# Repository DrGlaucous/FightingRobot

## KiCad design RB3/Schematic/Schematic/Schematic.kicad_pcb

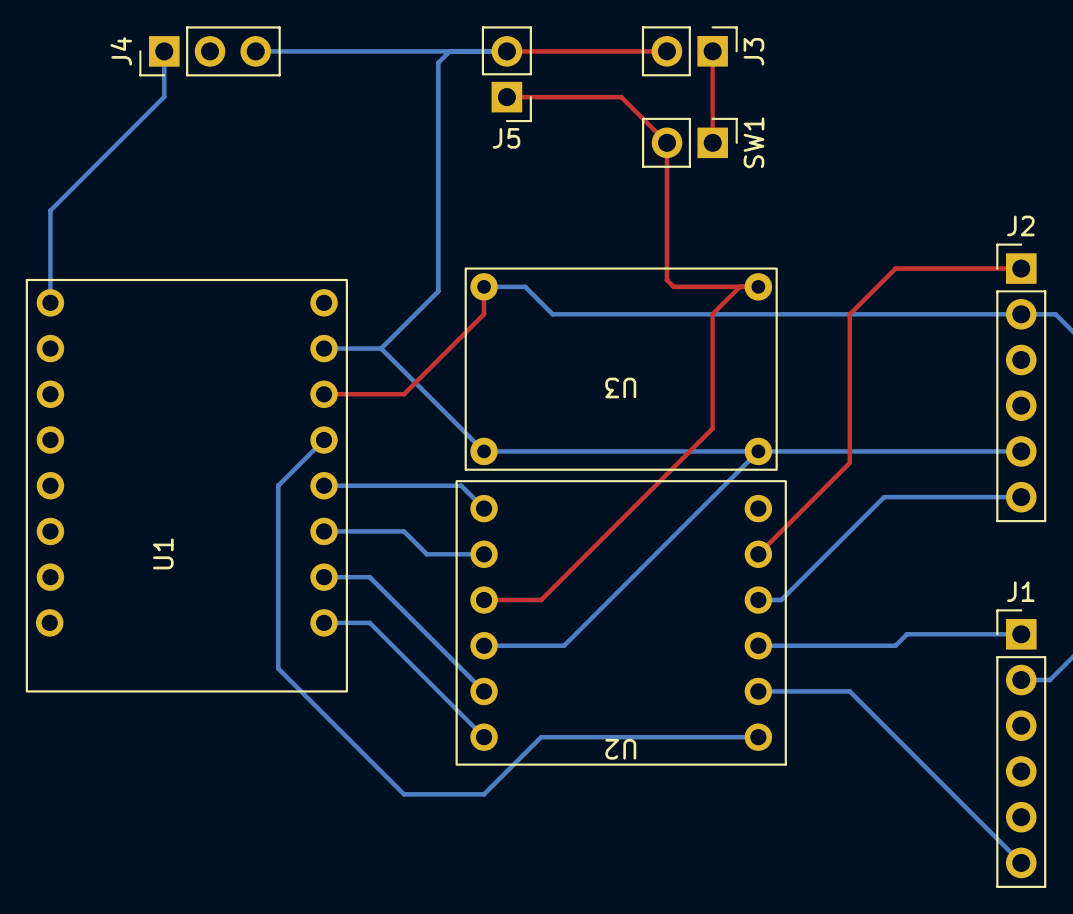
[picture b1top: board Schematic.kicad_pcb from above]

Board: 2 copper layers, 9 parts (0 on the bottom side), 18 nets.

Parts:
J1, J2: Motor 1; PinHeader_1x06_P2.54mm_Vertical
J3: Battery; PinHeader_1x02_P2.54mm_Vertical
J4: ESC; PinHeader_1x03_P2.54mm_Vertical
J5: ESC_PWR; PinHeader_1x02_P2.54mm_Vertical
SW1: MAIN_CUTOFF; PinHeader_1x02_P2.54mm_Vertical
U1: ESP32-C3-SuperMini_PLUS
U2: HW-627
U3: Mini360

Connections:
+3.3V: J1.2, J2.2, U1.14 (3v3), U3.4 (OUT)
+BATT: J3.1, SW1.1
/+BATT SW: J5.1, SW1.2, U2.9 (VMOT), U3.2 (IN)
/ESC: J4.1, U1.1 (D5)
/M1 A: J1.1 (Motor_2), U2.3 (OUT2)
/M1 B: J1.6 (M1), U2.2 (OUT1)
/M1 Control A: U1.9 (D0), U2.12 (IN4)
/M1 Control B: U1.10 (D1), U2.11 (IN3)
/M1 EA: J1.4, U1.5 (D9)
/M1 EB: J1.3, U1.4 (D8)
/M2 A: J2.1 (Motor_2), U2.5 (OUT4)
/M2 B: J2.6 (M1), U2.4 (OUT3)
/M2 Control A: U1.11 (D2), U2.8 (IN2)
/M2 Control B: U1.12 (D3), U2.7 (IN1)
/M2 EA: J2.4, U1.3 (D7)
/M2 EB: J2.3, U1.2 (D6)
/SLEEP: U1.13 (D4), U2.1 (SLEEP)
GND: J1.5, J2.5, J3.2, J4.3, J5.2, U1.15 (Gnd), U2.10 (GND), U3.1 (GND), U3.3 (GND)

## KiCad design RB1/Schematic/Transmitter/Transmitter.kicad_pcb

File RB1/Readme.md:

# Remote Vehicle repository

This is where I put everything relating to designing a small, "antweight" combat robot.

## Firmware
Currently, the firmware is programmed in platform.io around the STM32 architecture.
The vehicle communicates to the controller using the RFM69HW radio module, which is both inexpensive and has excellent transmission range.

The "Transmitter" module decodes [PPM signals](http://flyingeinstein.com/index.php/articles/58-ppm-explained) from the controller and sends their digital values over the radio to the vehicle. There *are* recievers that output PPM directly without the need for the RFM middleman, but those are expensive and radio-specific. The extra range those modules would provide would be moot in the context of miniature combat robots. The analog transmitters additionally do not provide the customization abillity the digital transmiter has.

The work with RFM69 radios builds upon my previous project where I made an [inexpensive iClicker alternative using just the radio and an STM32](https://github.com/DrGlaucous/LittleBuddy). That repository better outlines how the STM32 should be connected to the RFM69 module.

---

<details>
  <summary style="font-size:100%;"><i><b>Notes for me</b></i></summary>

### Future Goals
Either use an ESP32 on the vehicle-side, or add bidirectional DShot to the STM32, so the vehicle's motor will provide telemetry.

### Mobility
With the transmitter, more flexible motion can be implemented.

Current suggestion: 3 wheeled omniwheel wheelbase

### Weapons

Rotating offset platic blade on one side, must not be below or above the robot's dirve train so it can drive upside down or rightside up.

Or long, plastic wedge attached to a servo motor for flipping other robots.

</details>

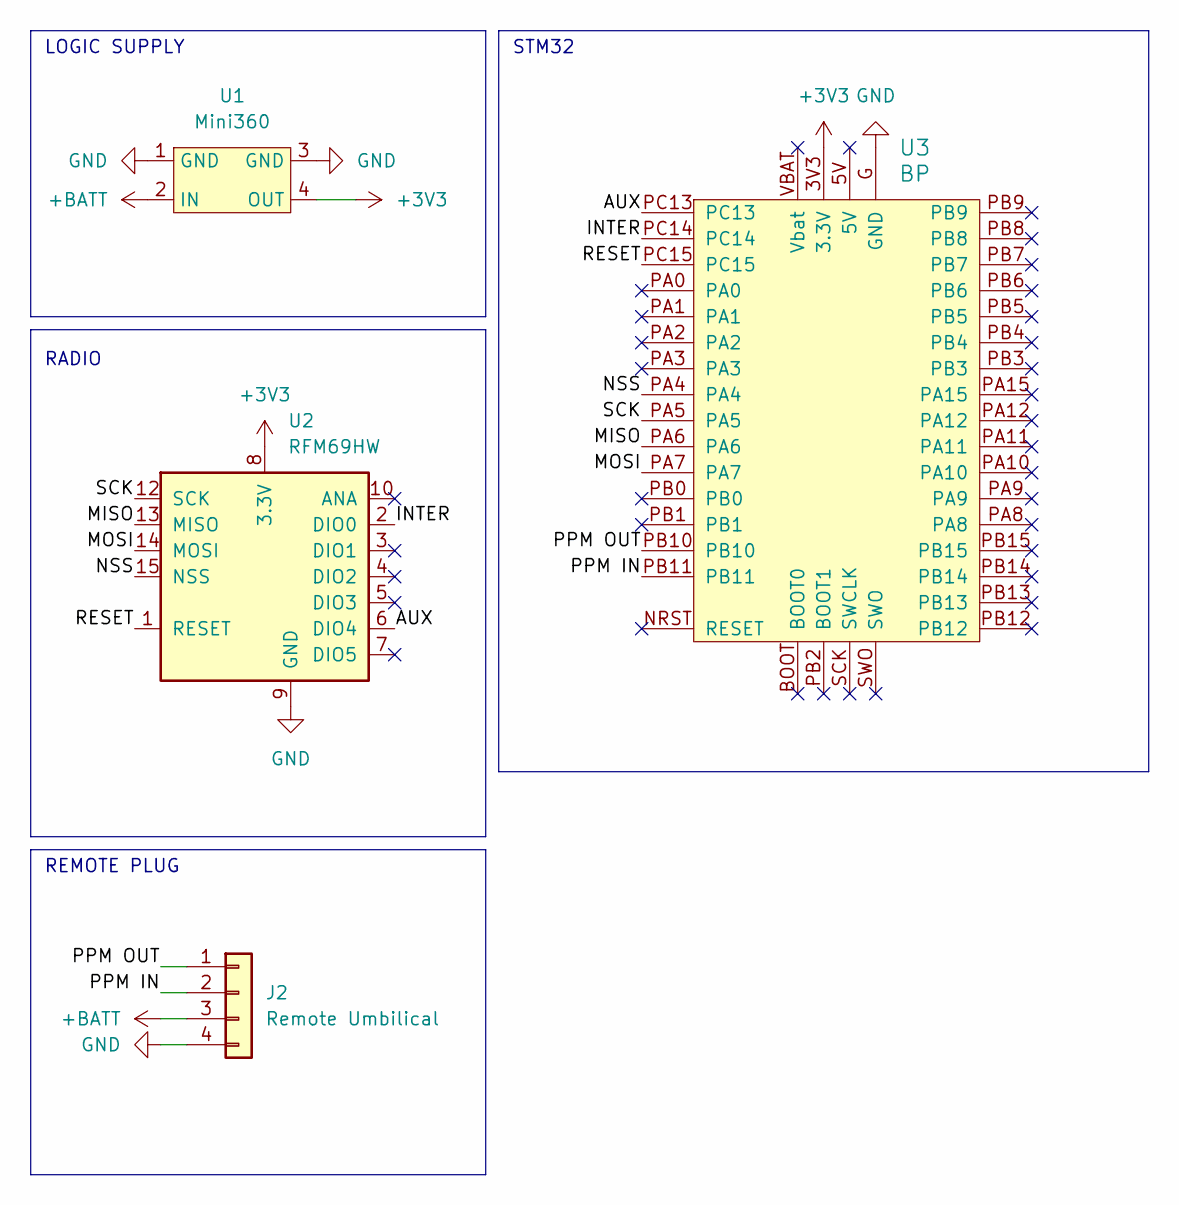
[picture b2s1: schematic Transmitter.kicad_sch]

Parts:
J2: Remote Umbilical; PinHeader_1x04_P2.54mm_Vertical
U1: Mini360
U2: RFM69HW; HOPERF_RFM69HW
U3: BP; blue_pill

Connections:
+3V3: U1.4 (OUT), U2.8 (3.3V), U3.3V3 (3.3V)
+BATT: J2.3, U1.2 (IN)
/AUX: U2.6 (DIO4), U3.PC13
/INTER: U2.2 (DIO0), U3.PC14
/MISO: U2.13 (MISO), U3.PA6
/MOSI: U2.14 (MOSI), U3.PA7
/NSS: U2.15 (NSS), U3.PA4
/PPM IN: J2.2, U3.PB11
/PPM OUT: J2.1, U3.PB10
/RESET: U2.1 (RESET), U3.PC15
/SCK: U2.12 (SCK), U3.PA5
GND: J2.4, U1.1 (GND), U1.3 (GND), U2.9 (GND), U2.11 (GND), U3.G (GND)

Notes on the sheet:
STM32
LOGIC SUPPLY
REMOTE PLUG
RADIO

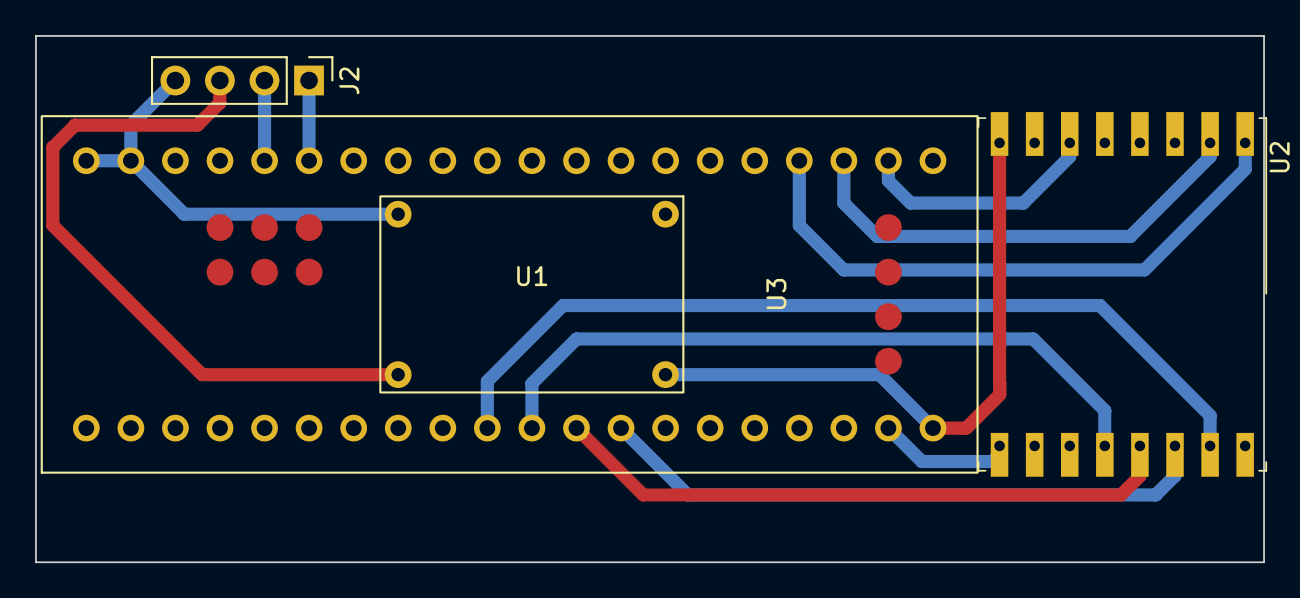
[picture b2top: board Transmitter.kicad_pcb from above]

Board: 2 copper layers, 70.0 x 30.0 mm, 4 parts (0 on the bottom side), 12 nets.

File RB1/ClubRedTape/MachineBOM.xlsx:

DO NOT ENTER VALUES FOR COLUMNS HIGHLIGHTED GREEN
Overall Bot Value: |  | 84.354499999999987 | External Component $ Spent: | 202.96 | Railside $ Spent: | 30.74 | Total $ Spent: | 233.7
Category | Qty | Item | Specs | Item Description | Vendor/Source | Link | Units per Package | Units per Bot | Provided by Railside? | Item Cost | What is the part for? | Unit Cost | Unit/Bot Cost | Total Cost
 | 1 | Fingertech Mini Power Switch | N.A. | Screw switch used to turn robot on / off | Itgresa | https://itgresa.com/product/mini-power-switch/ | 1 | 1 | yes | 7.99 | Required Safety | 7.99 | 7.99 | 7.99
 | 1 | Tattu 450 mAh 2S LiPo with XT30 | 75C 450mAh | Battery to power the robot | Amazon | https://www.amazon.com/TATTU-450mAh-Battery-Pack-H-Frame/dp/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 | 1 | 1 | yes | 12.95 | Power | 12.95 | 12.95 | 12.95
 | 1 | N20 gearmotor | 12 Volt, 1000 RPM | For Robot Drive Base | AliExpress | https://www.aliexpress.com/item/2251832836005412.html?spm=a2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 | 1 | 3 | no | 1.68 | Mobility | 1.68 | 5.04 | 1.68
 | 1 | N20 gearmotor (alt. source) | 12 Volt, 800 RPM | Alt. Club provided Drive Base motors | itgresa | https://itgresa.com/product/turnabot-n20-motors-1400rpm/ | 1 | 3 | yes | 9.8000000000000007 | Mobility (backup) | 9.8000000000000007 | 29.400000000000002 | 9.8000000000000007
 | 1 | RFM69HW Radio Tranciever | 915Mhz, 1.4kbps | For remote interfacing | AliExpress | https://www.aliexpress.com/item/3256803259645975.html?spm=a2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 | 1 | 2 | no | 1.66 | Remote Control | 1.66 | 3.32 | 1.66
Electronics | 1 | LittleBee ESC | BLHELI_S, 30A | For driving the weapon | Amazon | https://www.amazon.com/LITTLEBEE-Mulitshot-Oneshot42-OneShot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 | 4 | 1 | no | 30 | Weapon Driver | 7.5 | 7.5 | 30
 | 1 | 2205 Emax Motor | 2300KV, 2205 | Used as the weapon | Amazon | https://www.amazon.com/AKK-RS2205-Brushless-2300KV-Quadcopte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 | 4 | 1 | no | 31.99 | Weapon | 7.9974999999999996 | 7.9974999999999996 | 31.99
 | 1 | Fuse | 15A max | Overcurrent safety | Unknown |  | 2 | 2 | yes | 0 | Required Safety | 0 | 0 | 0
 | 1 | DRV8833 DC motor driver | handles 2 motors | For Robot Drive Base | AliExpress | https://www.aliexpress.com/item/3256806258295019.html?spm=a2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 | 10 | 2 | no | 4.6399999999999997 | Mobility | 0.46399999999999997 | 0.92799999999999994 | 4.6399999999999997
 | 1 | XL60009 Boost module | 4A in max, 12 volts out | Motor power supply | Amazon | https://www.amazon.com/AITRIP-Voltage-Adjustable-Step-up-Con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 | 10 | 1 | no | 14 | Power Regulation | 1.4 | 1.4 | 14
 | 1 | Mini360 Buck module | 3.3 volt out | Logic power supply | AliExpress | https://www.aliexpress.us/item/3256806205076602.html?spm=a2g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 | 20 | 1 | no | 2 | Power Regulation | 0.1 | 0.1 | 2
 | 1 | Lolin32 LITE | 32 bit microcontroller | Bot controller | AliExpress | https://www.aliexpress.com/item/3256801612417572.html?spm=a2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 | 1 | 1 | no | 2.12 | Bot Control | 2.12 | 2.12 | 2.12
 | 1 | STM32 Bluepill | 32 bit microcontroller | Transmitter controller | AliExpress | https://www.aliexpress.us/item/3256806245533637.html?spm=a2g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 | 10 | 1 | no | 14 | Remote Control | 1.4 | 1.4 | 14
 | 1 | MG90S Servo | All-metal MG90S | micro servo | AliExpress | https://www.aliexpress.com/item/3256805876746809.html?spm=a2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 | 10 | 2 | no | 16.37 | Weapon | 1.637 | 3.274 | 16.37
 |  | Things like power transmission members (belts, pulleys), bot materials (3D prin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 |  |  |  |  |  |  |  | 0 |  | 0 | 0 | 0
 | 1 | ABS (Home-Extruded) | PA757 | Natural uncolored ABS | Filastruder |  | 50 | 0.5 | no | 80 | Frame | 1.6 | 0.8 | 80
Structure / Materials | 1 |  |  |  |  |  |  |  |  | 0 |  | 0 | 0 | 0
 | 1 |  |  |  |  |  |  |  |  | 0 |  | 0 | 0 | 0
 | 1 |  |  |  |  |  |  |  |  | 0 |  | 0 | 0 | 0
 |  | Screws, nuts, shoulder bolts go here |  |  |  |  |  |  |  | 0 |  | 0 | 0 | 0
 | 1 | 6-32x1-1/2 Phillips screw | 6-32x1-1/2 | Machine screw | Menards | In-store | 100 | 3 | no | 2.25 | Fasteners | 2.2499999999999999E-2 | 6.7500000000000004E-2 | 2.25
Hardware (Fasteners) | 1 | 6-32 Hex Nut | 6-32 size | Machine nut | Menards | In-Store | 100 | 3 | no | 2.25 | Fasteners | 2.2499999999999999E-2 | 6.7500000000000004E-2 | 2.25
 | 1 | Plastic Screw | #4 | self-tapping screw | Amazon | https://www.amazon.com/Thread-Rolling-Plastic-Finish-Degree/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 | 100 | 50 | yes | 0 | Fasteners | 0 | 0 | 0
 |  |  |  |  |  |  |  |  |  | 0 |  | 0 | 0 | 0
 |  | Anything that doesnt fit into the above category |  |  |  |  |  |  |  | 0 |  | 0 | 0 | 0
 |  |  |  |  |  |  |  |  |  | 0 |  | 0 | 0 | 0
Misc. |  |  |  |  |  |  |  |  |  | 0 |  | 0 | 0 | 0
 |  |  |  |  |  |  |  |  |  | 0 |  | 0 | 0 | 0
 |  |  |  |  |  |  |  |  |  | 0 |  | 0 | 0 | 0
 |  |  |  |  |  |  |  |  |  | 0 |  | 0 | 0 | 0
 |  |  |  |  |  |  |  |  |  | 0 |  | 0 | 0 | 0
 |  |  |  |  |  |  |  |  |  | 0 |  | 0 | 0 | 0
 |  |  |  |  |  |  |  |  |  | 0 |  | 0 | 0 | 0
 |  |  |  |  |  |  |  |  |  | 0 |  | 0 | 0 | 0
 |  |  |  |  |  |  |  |  |  | 0 |  | 0 | 0 | 0
 |  |  |  |  |  |  |  |  |  | 0 |  | 0 | 0 | 0
 |  |  |  |  |  |  |  |  |  | 0 |  | 0 | 0 | 0
 |  |  |  |  |  |  |  |  |  | 0 |  | 0 | 0 | 0
 |  |  |  |  |  |  |  |  |  | 0 |  | 0 | 0 | 0
 |  |  |  |  |  |  |  |  |  | 0 |  | 0 | 0 | 0
 |  |  |  |  |  |  |  |  |  | 0 |  | 0 | 0 | 0
 |  |  |  |  |  |  |  |  |  | 0 |  | 0 | 0 | 0

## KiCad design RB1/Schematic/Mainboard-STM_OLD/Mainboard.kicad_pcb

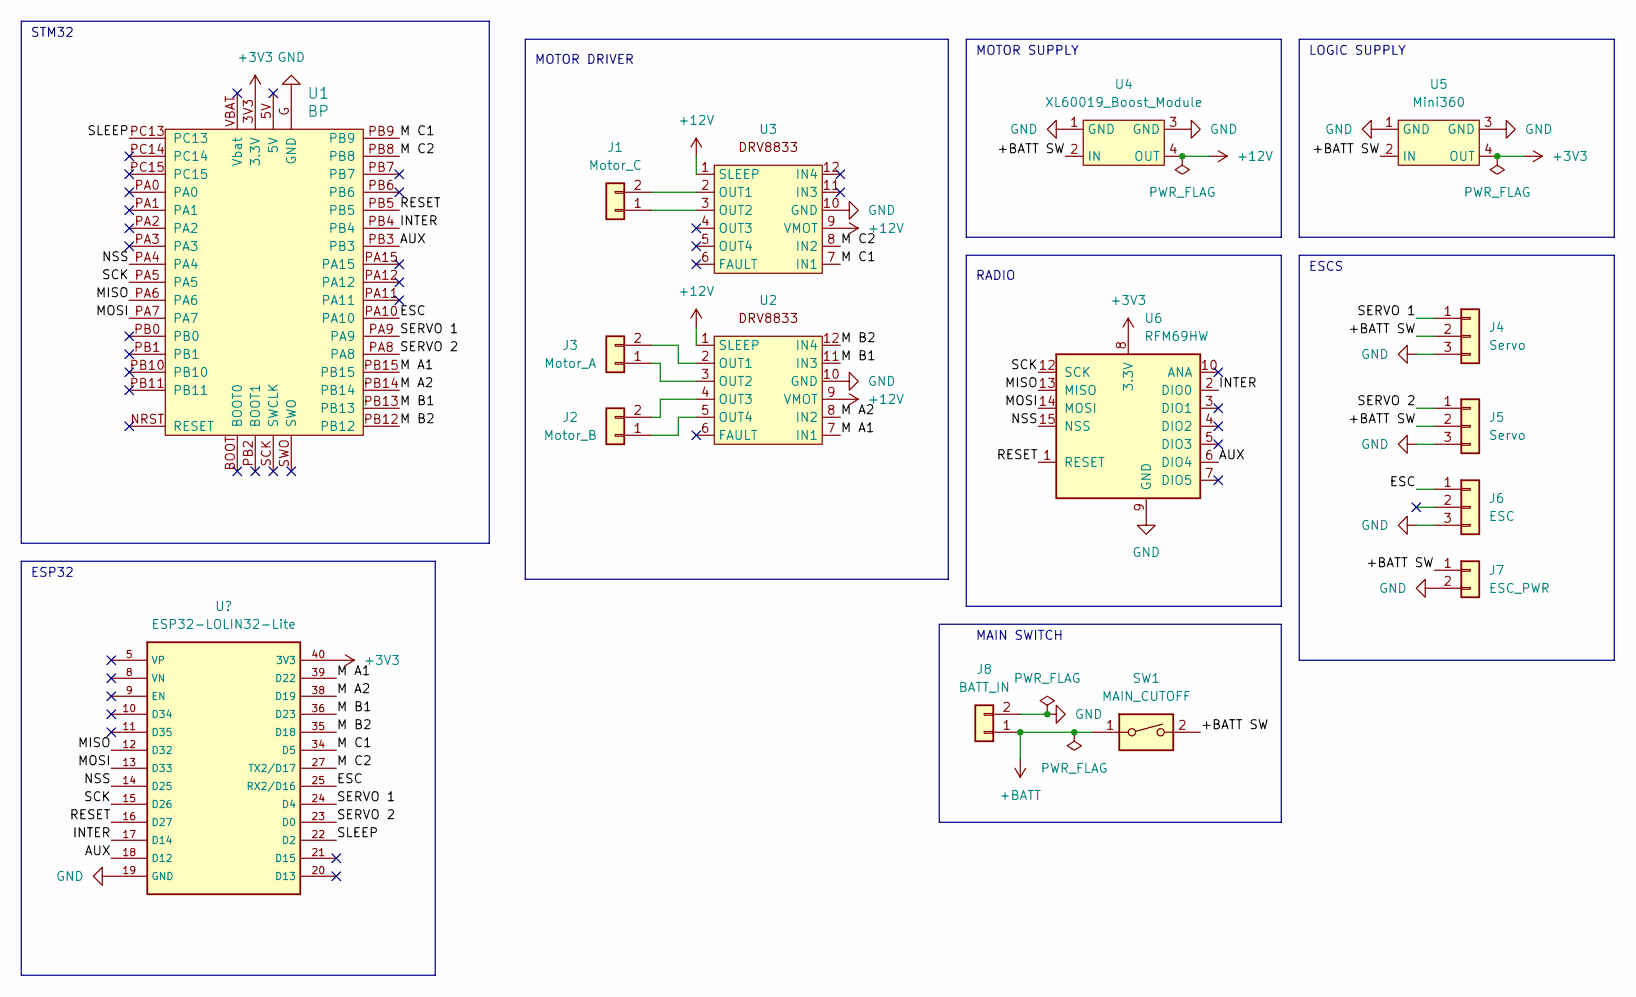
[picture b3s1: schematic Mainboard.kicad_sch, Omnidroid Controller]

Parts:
J1: Motor_C; PinHeader_1x02_P2.54mm_Vertical
J2: Motor_B; PinHeader_1x02_P2.54mm_Vertical
J3: Motor_A; PinHeader_1x02_P2.54mm_Vertical
J4, J5: Servo; PinHeader_1x03_P2.54mm_Vertical
J6: ESC; PinHeader_1x03_P2.54mm_Vertical
J7: ESC_PWR; PinHeader_1x02_P2.54mm_Vertical
J8: BATT_IN; PinHeader_1x02_P2.54mm_Vertical
SW1: MAIN_CUTOFF; PinHeader_1x02_P2.54mm_Vertical
U1: BP; blue_pill
U2, U3: HW-627
U4: XL60019_Boost_Module; XL60019 Boost Module
U5: Mini360
U6: RFM69HW; HOPERF_RFM69HW
U8: ESP32-LOLIN32-Lite

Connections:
+3V3: U1.3V3 (3.3V), U5.4 (OUT), U6.8 (3.3V), U8.40 (3V3)
+12V: U2.1 (SLEEP), U2.9 (VMOT), U3.1 (SLEEP), U3.9 (VMOT), U4.4 (OUT)
+BATT: J8.1, SW1.1
/+BATT SW: J4.2, J5.2, J7.1, SW1.2, U4.2 (IN), U5.2 (IN)
/AUX: U1.PB3, U6.6 (DIO4), U8.18 (D12)
/ESC: J6.1, U1.PA10, U8.25 (RX2/D16)
/INTER: U1.PB4, U6.2 (DIO0), U8.17 (D14)
/M A1: U1.PB15, U2.7 (IN1), U8.39 (D22)
/M A2: U1.PB14, U2.8 (IN2), U8.38 (D19)
/M B1: U1.PB13, U2.11 (IN3), U8.36 (D23)
/M B2: U1.PB12, U2.12 (IN4), U8.35 (D18)
/M C1: U1.PB9, U3.7 (IN1), U8.34 (D5)
/M C2: U1.PB8, U3.8 (IN2), U8.27 (TX2/D17)
/MISO: U1.PA6, U6.13 (MISO), U8.12 (D32)
/MOSI: U1.PA7, U6.14 (MOSI), U8.13 (D33)
/NSS: U1.PA4, U6.15 (NSS), U8.14 (D25)
/RESET: U1.PB5, U6.1 (RESET), U8.16 (D27)
/SCK: U1.PA5, U6.12 (SCK), U8.15 (D26)
/SERVO 1: J4.1, U1.PA9, U8.24 (D4)
/SERVO 2: J5.1, U1.PA8, U8.23 (D0)
/SLEEP: U1.PC13, U8.22 (D2)
GND: J4.3, J5.3, J6.3, J7.2, J8.2, U1.G (GND), U2.10 (GND), U3.10 (GND), U4.1 (GND), U4.3 (GND), U5.1 (GND), U5.3 (GND), U6.9 (GND), U6.11 (GND), U8.19 (GND)
unnamed: J1.1, U3.3 (OUT2)
unnamed: J1.2, U3.2 (OUT1)
unnamed: J2.1, U2.5 (OUT4)
unnamed: J2.2, U2.4 (OUT3)
unnamed: J3.1, U2.3 (OUT2)
unnamed: J3.2, U2.2 (OUT1)

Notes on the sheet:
ESP32
RADIO
ESCS
MAIN SWITCH
STM32
MOTOR DRIVER
MOTOR SUPPLY
LOGIC SUPPLY

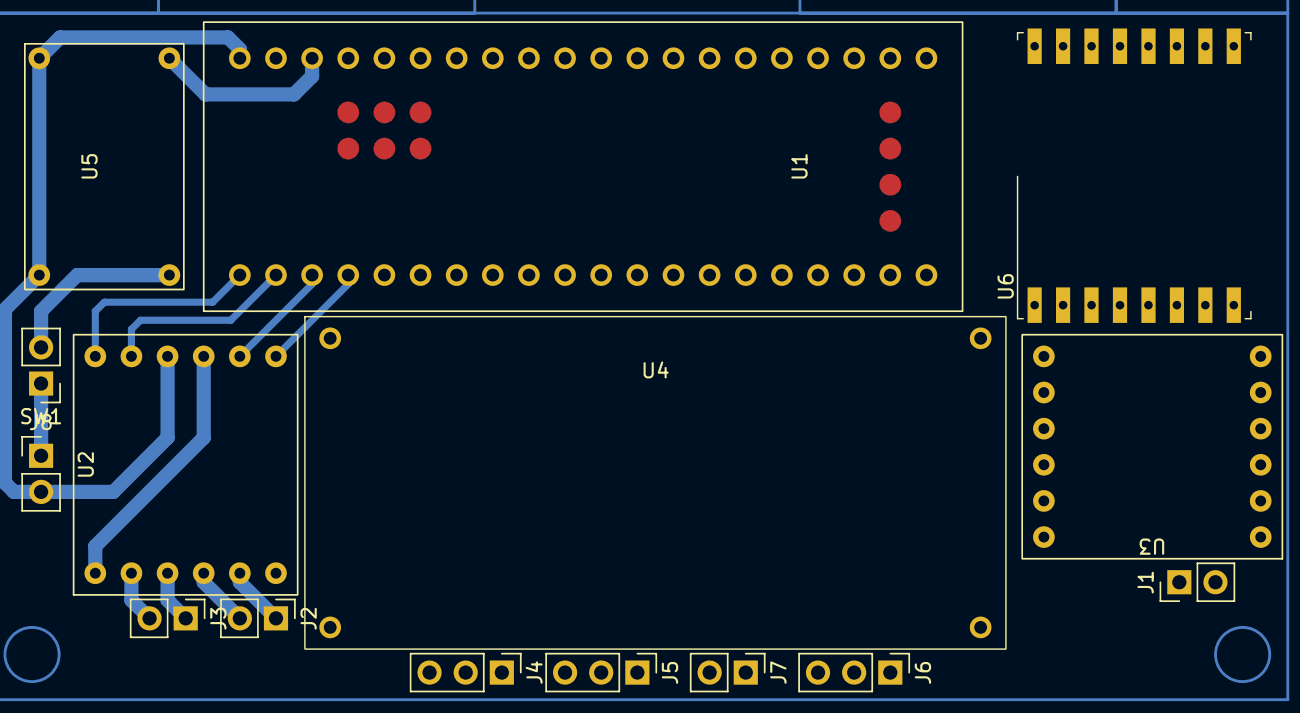
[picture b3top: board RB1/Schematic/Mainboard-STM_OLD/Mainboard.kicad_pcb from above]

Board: 2 copper layers, 15 parts (0 on the bottom side), 27 nets.

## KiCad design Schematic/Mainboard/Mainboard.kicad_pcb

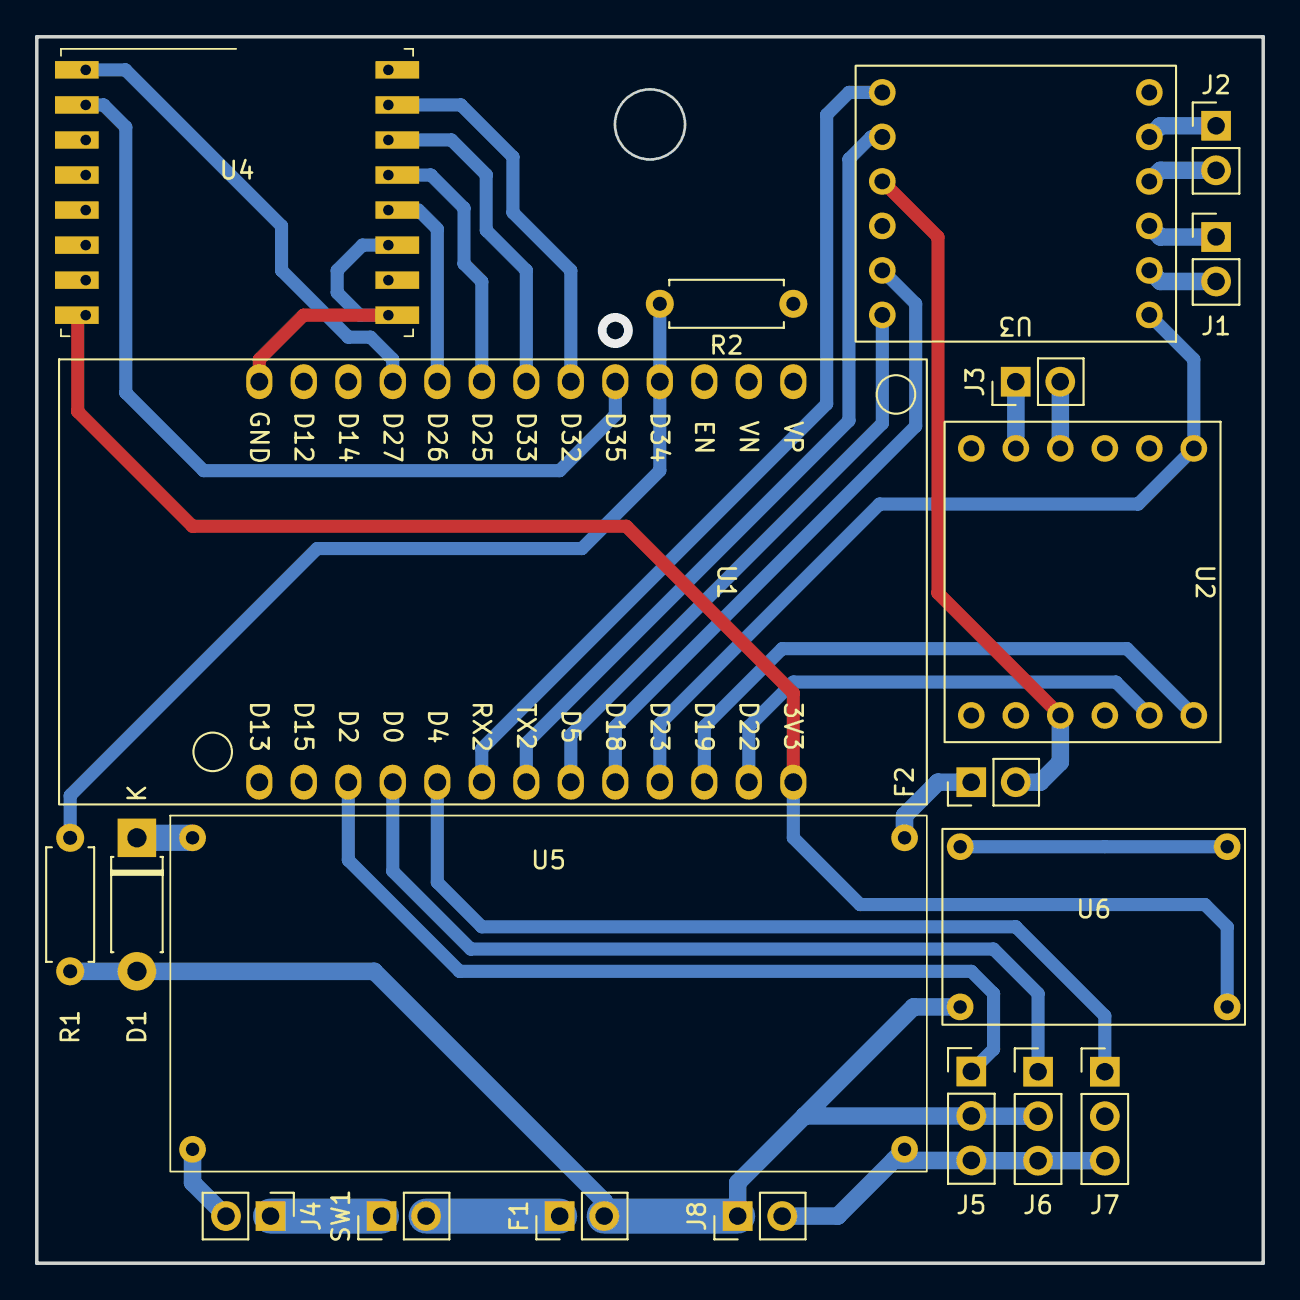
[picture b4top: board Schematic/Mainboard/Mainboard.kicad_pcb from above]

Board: 2 copper layers, 70.0 x 70.0 mm, 20 parts (0 on the bottom side), 31 nets.

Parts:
D1: 1N4007; D_DO-41_SOD81_P7.62mm_Horizontal
F1, F2: Fuse 15A; PinHeader_1x02_P2.54mm_Vertical
J1: Motor_A; PinHeader_1x02_P2.54mm_Vertical
J2: Motor_B; PinHeader_1x02_P2.54mm_Vertical
J3: Motor_C; PinHeader_1x02_P2.54mm_Vertical
J4: BATT_IN; PinHeader_1x02_P2.54mm_Vertical
J5, J6: Servo; PinHeader_1x03_P2.54mm_Vertical
J7: ESC; PinHeader_1x03_P2.54mm_Vertical
J8: ESC_PWR; PinHeader_1x02_P2.54mm_Vertical
R1: 150k Ohm; R_Axial_DIN0207_L6.3mm_D2.5mm_P7.62mm_Horizontal
R2: 10k Ohm; R_Axial_DIN0207_L6.3mm_D2.5mm_P7.62mm_Horizontal
SW1: MAIN_CUTOFF; PinHeader_1x02_P2.54mm_Vertical
U1: ESP32-LOLIN32-Lite
U2, U3: HW-627
U4: RFM69HW; HOPERF_RFM69HW
U5: XL60019_Boost_Module; XL60019 Boost Module
U6: Mini360

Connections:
+3V3: U1.40 (3V3), U4.8 (3.3V), U6.4 (OUT)
+10V: F2.2, U2.9 (VMOT), U3.9 (VMOT)
+BATT: J4.1, SW1.1
/+BATT SW: D1.2 (A), F1.2, J5.2, J6.2, J8.1, R1.2, U6.2 (IN)
/BAT READ: R1.1, R2.2, U1.10 (D34)
/ESC: J7.1, U1.24 (D4)
/INTER: U1.11 (D35), U4.2 (DIO0)
/M A1: U1.25 (RX2/D16), U3.7 (IN1)
/M A2: U1.27 (TX2/D17), U3.8 (IN2)
/M B1: U1.35 (D18), U3.11 (IN3)
/M B2: U1.34 (D5), U3.12 (IN4)
/M C1: U1.39 (D22), U2.11 (IN3)
/M C2: U1.38 (D19), U2.12 (IN4)
/MISO: U1.14 (D25), U4.13 (MISO)
/MOSI: U1.13 (D33), U4.14 (MOSI)
/NSS: U1.12 (D32), U4.15 (NSS)
/RESET: U1.16 (D27), U4.1 (RESET)
/SCK: U1.15 (D26), U4.12 (SCK)
/SERVO 1: J5.1, U1.22 (D2)
/SERVO 2: J6.1, U1.23 (D0)
/SLEEP: U1.36 (D23), U2.1 (SLEEP), U3.1 (SLEEP)
GND: J4.2, J5.3, J6.3, J7.3, J8.2, R2.1, U1.19 (GND), U2.10 (GND), U3.10 (GND), U4.9 (GND), U4.11 (GND), U5.1 (GND), U5.3 (GND), U6.1 (GND), U6.3 (GND)
unnamed: D1.1 (K), U5.2 (IN)
unnamed: F1.1, SW1.2
unnamed: J1.1, U3.3 (OUT2)
unnamed: J1.2, U3.2 (OUT1)
unnamed: J2.1, U3.5 (OUT4)
unnamed: J2.2, U3.4 (OUT3)
unnamed: J3.1, U2.5 (OUT4)
unnamed: J3.2, U2.4 (OUT3)
unnamed: F2.1, U5.4 (OUT)

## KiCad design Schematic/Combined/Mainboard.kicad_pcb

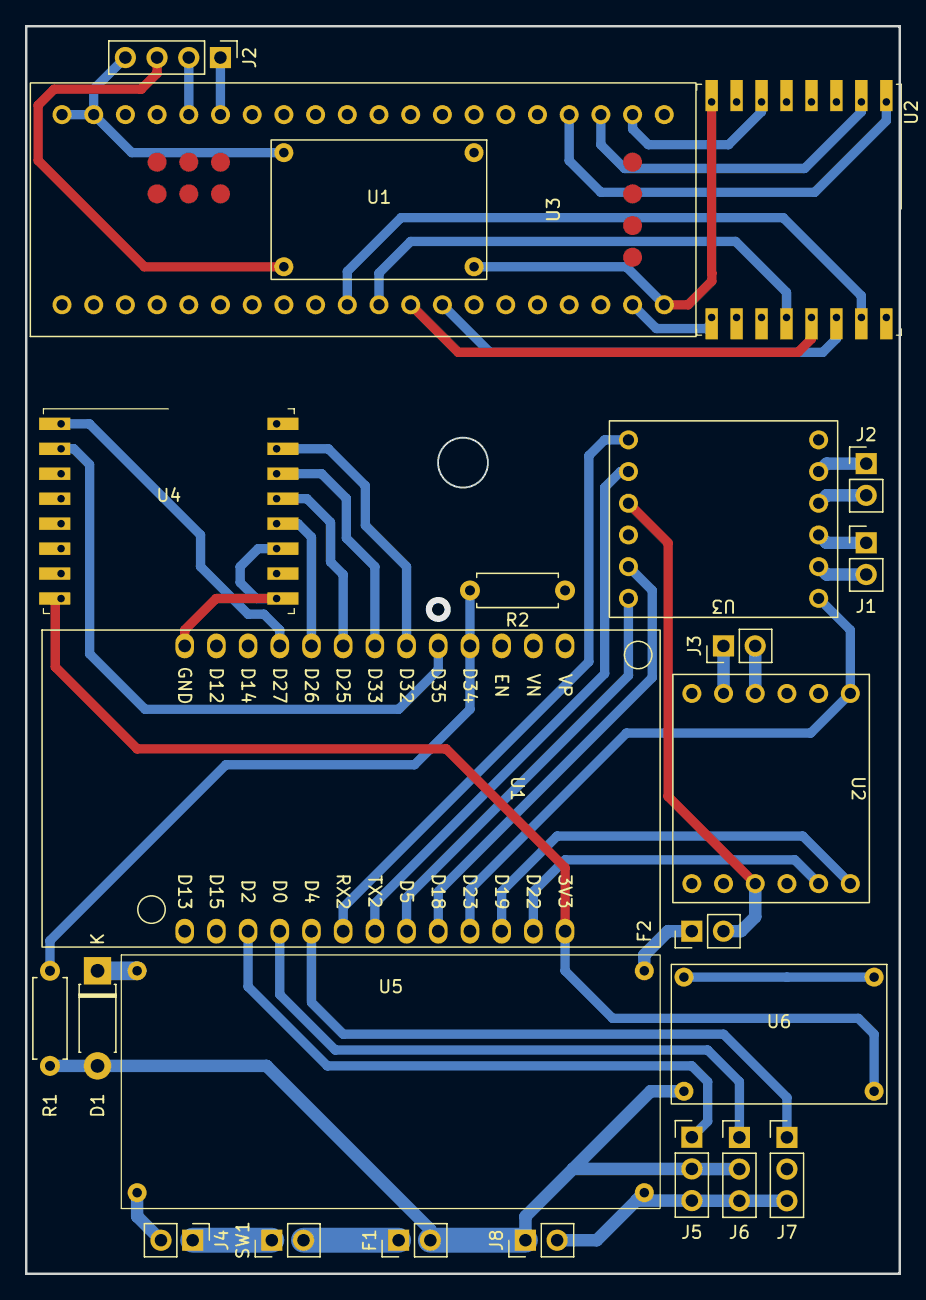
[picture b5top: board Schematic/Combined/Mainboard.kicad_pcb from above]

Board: 2 copper layers, 70.0 x 100.0 mm, 24 parts (0 on the bottom side), 31 nets.

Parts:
D1: 1N4007; D_DO-41_SOD81_P7.62mm_Horizontal
F1, F2: Fuse 15A; PinHeader_1x02_P2.54mm_Vertical
J1: Motor_A; PinHeader_1x02_P2.54mm_Vertical
J2: Motor_B; PinHeader_1x02_P2.54mm_Vertical
J2#2: Remote Umbilical; PinHeader_1x04_P2.54mm_Vertical
J3: Motor_C; PinHeader_1x02_P2.54mm_Vertical
J4: BATT_IN; PinHeader_1x02_P2.54mm_Vertical
J5, J6: Servo; PinHeader_1x03_P2.54mm_Vertical
J7: ESC; PinHeader_1x03_P2.54mm_Vertical
J8: ESC_PWR; PinHeader_1x02_P2.54mm_Vertical
R1: 150k Ohm; R_Axial_DIN0207_L6.3mm_D2.5mm_P7.62mm_Horizontal
R2: 10k Ohm; R_Axial_DIN0207_L6.3mm_D2.5mm_P7.62mm_Horizontal
SW1: MAIN_CUTOFF; PinHeader_1x02_P2.54mm_Vertical
U1: ESP32-LOLIN32-Lite
U1#2, U6: Mini360
U2, U4: RFM69HW; HOPERF_RFM69HW
U2#2, U3#2: HW-627
U3: BP; blue_pill
U5: XL60019_Boost_Module; XL60019 Boost Module

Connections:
+3V3: U1.40 (3V3), U1#2.4 (OUT), U2.8 (3.3V), U3.3V3 (3.3V), U4.8 (3.3V), U6.4 (OUT)
+10V: F2.2, U2#2.9 (VMOT), U3#2.9 (VMOT)
+BATT: J2#2.3, J4.1, SW1.1, U1#2.2 (IN)
/+BATT SW: D1.2 (A), F1.2, J5.2, J6.2, J8.1, R1.2, U6.2 (IN)
/BAT READ: R1.1, R2.2, U1.10 (D34)
/ESC: J7.1, U1.24 (D4)
/INTER: U1.11 (D35), U2.2 (DIO0), U3.PC14, U4.2 (DIO0)
/M A1: U1.25 (RX2/D16), U3#2.7 (IN1)
/M A2: U1.27 (TX2/D17), U3#2.8 (IN2)
/M B1: U1.35 (D18), U3#2.11 (IN3)
/M B2: U1.34 (D5), U3#2.12 (IN4)
/M C1: U1.39 (D22), U2#2.11 (IN3)
/M C2: U1.38 (D19), U2#2.12 (IN4)
/MISO: U1.14 (D25), U2.13 (MISO), U3.PB4, U4.13 (MISO)
/MOSI: U1.13 (D33), U2.14 (MOSI), U3.PB5, U4.14 (MOSI)
/NSS: U1.12 (D32), U2.15 (NSS), U3.PA15, U4.15 (NSS)
/RESET: U1.16 (D27), U2.1 (RESET), U3.PC15, U4.1 (RESET)
/SCK: U1.15 (D26), U2.12 (SCK), U3.PB3, U4.12 (SCK)
/SERVO 1: J5.1, U1.22 (D2)
/SERVO 2: J6.1, U1.23 (D0)
/SLEEP: U1.36 (D23), U2#2.1 (SLEEP), U3#2.1 (SLEEP)
GND: J2#2.4, J4.2, J5.3, J6.3, J7.3, J8.2, R2.1, U1.19 (GND), U1#2.1 (GND), U1#2.3 (GND), U2.9 (GND), U2.11 (GND), U2#2.10 (GND), U3.G (GND), U3#2.10 (GND), U4.9 (GND), U4.11 (GND), U5.1 (GND), U5.3 (GND), U6.1 (GND), U6.3 (GND)
unnamed: D1.1 (K), U5.2 (IN)
unnamed: F1.1, SW1.2
unnamed: J1.1, U3#2.3 (OUT2)
unnamed: J1.2, U3#2.2 (OUT1)
unnamed: J2.1, U3#2.5 (OUT4)
unnamed: J2.2, U3#2.4 (OUT3)
unnamed: J3.1, U2#2.5 (OUT4)
unnamed: J3.2, U2#2.4 (OUT3)
unnamed: F2.1, U5.4 (OUT)

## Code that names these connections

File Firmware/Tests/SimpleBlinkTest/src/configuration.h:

//Configuration



////////RADIO SETTINGS////////

// Addresses for this node. CHANGE THESE FOR EACH NODE!

#define NETWORKID           0   // Must be the same for all nodes
#define RECEIVERNODEID      1   //node the transmitter lives on
#define TRANSMITTERNODEID   2   //node the robot lives on


//#define FREQUENCY   RF69_433MHZ
#define FREQUENCY     RF69_915MHZ
#define IS_HIGH_POWER true

//pins for the radio
#ifdef USING_STM32_BP
    //final setup
    #define SLAVE_PIN PA4
    #define IRQ_PIN PC14

    //testing setup (littleBuddies)
    //#define SLAVE_PIN PA4
    //#define IRQ_PIN PB4

#elif USING_ESP32
    #define SLAVE_PIN 32
    #define IRQ_PIN 35

    #define SPI_SCK_PIN 26
    #define SPI_MISO_PIN 25
    #define SPI_MOSI_PIN 33
    #define SPI_NSS_PIN SLAVE_PIN
#endif



#define ENCRYPT       true // Set to "true" to use encryption
#define ENCRYPTKEY    "HOTCRYSTALBABESS" //"TOPSECRETPASSWRD" // Use the same 16-byte key on all nodes

// Use ACKnowledge when sending messages (or not):
#define USEACK        true // Request ACKs or not


////////BEHAVIOR SETTINGS////////

//what end of the stick the firmware is on (moved to INI)
//#define IS_CONTROLLER


////////////////PPM SETTINGS////////////////

//for processing and sending out remote control channel data

//how many analog channels we have
#define ANALOG_CHANNEL_CNT 8
//how many grouped digital channels we have (2 digital inputs per channel, due to how futaba remotes work)
#define DIGITAL_CHANNEL_CNT 4

#define CHANNEL_COUNT ANALOG_CHANNEL_CNT + DIGITAL_CHANNEL_CNT

//the range of the normalized analog values (mapped between [0,this], exclusive? or --inclusive?)
//adding detune will not affect these values
#define NORMAL_MIN 0
#define NORMAL_MAX 512


//PPM config stuff is only really needed for the transmitter
#ifdef IS_CONTROLLER

    //////NORMALIZATION CONSTANTS

    //min and max values read from PPM (WITHOUT DETUNE)
    #define ANALOG_MIN_LIM 550
    #define ANALOG_MAX_LIM 970


    //+- this ammount when calculating digital sums (realtive to raw PPM input)
    #define NORMAL_NOISE_ERR 5
    //+- this ammount when the aux. switch is flipped (main switches use (ANALOG_MAX_LIM - ANALOG_MIN_LIM)/2)
    #define DETUNE_VAL_SHIFT 64


    //////PPM LIBRARY CONFIG CONSTANTS
    //trigger on falling edge instead of rising edge (for futaba's weird 12 channel format)
    #define PPM_IS_INVERTED true

#ifdef USING_STM32_BP
    #define PPM_INTURRUPT_PIN PB11
#elif USING_ESP32
    #define PPM_INTURRUPT_PIN 27
#endif
    #define PPM_CHANNEL_COUNT CHANNEL_COUNT
    #define PPM_BLANK_TIME 5000
    #define PPM_MAX_WAIT_VALUE 1100
    #define PPM_MIN_WAIT_VALUE 400

    //default 8 channel
    //#define PPM_BLANK_TIME 2100
    //#define PPM_MAX_WAIT_VALUE 2000
    //#define PPM_MIN_WAIT_VALUE 1000
    //#define PPM_IS_INVERTED false

#else
    //something
    #define KAKAJAMANGA

    //for the STM32, random pins are used for testing: this part of the code will be used on the ESP32


    //no radio transmission for 1 second, robot shuts off
    #define KEEPALIVE_TIMEOUT_MS 1000

    //slope mapping based on experimetnal data and resistor values (TODO: make this parametric)
    #define VOLTMETER_SLOPE 0.0126 + 2.25

    //h-bridge operation:
    //HI-HI is break
    //LO-LO is no connection
    //HI-LO is dir 1
    //LO-HI is dir 2

#ifdef USING_STM32_BP
    //DRIVEBASE PINS
    #define MOTOR_1A_PIN PB0
    #define MOTOR_1B_PIN PB0

    #define MOTOR_2A_PIN PB0
    #define MOTOR_2B_PIN PB0

    #define MOTOR_3A_PIN PB0
    #define MOTOR_3B_PIN PB0

    #define MOTOR_SLEEP_PIN PB0

    #define VOLTMETER_PIN PB0


    //WEAPON PINS
    #define SERVO_1_PIN PB14
    #define SERVO_2_PIN PB15
    #define ESC_PIN PA8

#elif USING_ESP32
    //DRIVEBASE PINS

    //is 1, should be 3
    #define MOTOR_3A_PIN 17
    #define MOTOR_3B_PIN 16

    //is 2, should be 1
    #define MOTOR_1A_PIN 18
    #define MOTOR_1B_PIN 5

    //is 3, should be 2
    #define MOTOR_2A_PIN 19
    #define MOTOR_2B_PIN 22

    #define MOTOR_SLEEP_PIN 23


    //WEAPON PINS
    #define SERVO_1_PIN 2
    #define SERVO_2_PIN 0
    #define ESC_PIN 4

    //OTHER
    #define VOLTMETER_PIN 34

#endif

    //control surface mapping
    
    //analog
    #define X_IN 0
    #define Y_IN 1
    #define TURN_IN 3
    #define SERVO_IN 2
    #define ESC_IN 4
    #define SERVO_MIN_IN 7
    #define SERVO_MAX_IN 8
    
    //digital
    #define FLIPOVER_IN 0
    #define ESC_REVERSE_IN 1
    #define TWO_MODE_IN 2
    #define TWO_SELECT_IN 3

    //normalization

    //analog pins go from 0-255, so this must be within that range
    #define XY_RADIUS 0xFF

    #define SERVO_MIN 0
    #define SERVO_MAX 180
    //range of motion on one side (depricated in favor of making this adjustable using the knobs on the remote)
    //#define SERVO_RANGE 100

    //number of magnets in the motor (for erpm measurements, only used in dshot mode)
    #define MOTOR_POLE_COUNT 14

#ifdef USING_STM32_BP
    //PWM speeds
    #define ESC_SPEED_MIDDLE 0 //'0' in 3D mode
    //full speed in 3D mode
    #define ESC_SPEED_MIN 0
    #define ESC_SPEED_MAX 180
#elif USING_ESP32
    //dshot speeds (better than PWM, but only works with the dshot library)
    #define ESC_SPEED_MIDDLE 1024 //'0' in 3D mode
    //full speed in 3D mode
    #define ESC_SPEED_MIN 48
    #define ESC_SPEED_MAX 2048
#endif






#endif

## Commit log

2024-01-24 begin framework for main program
2024-01-24 oops: wrong folder
    swap final and test project
2024-01-24 add algorithm tester
    for debugging in depth on a PC
2024-01-25 begin work on SINE optimization
2024-01-26 work on remote program code
2024-01-31 Add rolled back firmware to debug main
    this firmware is known to transmit packets successfully
2024-01-31 Begin hardware layout
2024-02-01 CAD updates
2024-02-02 begin schematic work
2024-02-02 updates to CAD and schematic
2024-02-02 more schematic updates
2024-02-02 PCB work
    trying to cram everything on there
2024-02-05 finish omniwheel design
    begin work on main frame
2024-02-07 shift from STM32 to ESP32
    on the robot control surface
2024-02-08 update schematic and CAD
2024-02-09 cad and pcb updates
2024-02-10 finish first revision PCB
2024-02-10 stand by... resolving conflicts (pt. 2)
2024-02-11 rework radio class
    telemetry packets now come as part of the ACK, so there is less chance of both transmitters stepping on each other.
2024-02-12 finished proper radio functionality
2024-02-13 begin work on transmitter PCB
2024-02-13 begin adding ppm normalization code
2024-02-14 Add transmitter PCB
2024-02-14 edit bom, work on normalizing PPM
2024-02-14 some CAD and ppm timing documentation
    begin transferring PPM and transmitter routines to specialized classes
2024-02-16 fix problems with PPM libarary
    it was a controller problem, but the PPM reader needs to know how to see it.
2024-02-16 initial outlier processing removal
    still exist in-code, but is commented out
2024-02-17 last working state before major changes
    I changed a lot. it broke the transmission again. The code here is the last state where it works.
2024-02-17 major program updates (working)
    Transmitter is now properly normalized and working in both directions reliably.
2024-02-19 set up radio module on ESP32
    also worked on getting the ESP32 debugger up and running
2024-02-22 Work on weight reduction
    thin the shell in order to get the total weight under 1 lb.
2024-02-22 prepare to mill PCB
    also add more sub-functions to firmware
2024-02-22 push PCB back to other computer
    flatcam is crashing on my laptop, but works on my desktop...
2024-02-22 combine schematics into a single PCB layout
2024-02-28 begin physical construction
    also attempt to iron out bugs using STM32's alternate SPI pins
2024-02-28 finish PCB
    add gerbers and update schematics
2024-02-29 Port CAD to Solidworks
    Required for club certification.
    Don't get me started. I hold a strong opinion on Solidworks, to say the least.
2024-02-29 Work on transmitter breakout
2024-03-02 work out RX/TX kinks
    final radio and final baseboard now transmit properly
2024-03-03 Angle arm screws for assembly
2024-03-04 move updated library to PPM test project
2024-03-04 set up testing env to work with arduino and stm32
2024-03-04 revise frame and export STLs
2024-03-07 add no-transmit on no-ppm condition
    still having other numerous software bugs
2024-03-08 some small tweaks
2024-03-09 try to iron out bugs in the program code
    some of these bugs were hardware bugs...
2024-03-09 begin work on ESP-Now protocol
    this may be more reliable than the RFM69s
2024-03-12 finish value transmission with ESPNow
    reliable data transfer using ESPNow is now possible
2024-03-12 set up robot handling code
    discovered stability problems with the PPM portion of the radio code, will look into that next
2024-03-12 begin debugging ppm read interrupt conflicts
    interrupts are conflicting with the esp-now transmission, so we need to find a way to schedule them around each other. (sending esp-now packets throws off PPM readings considerably)
2024-03-12 fixed PPM conflict
    add halt states to PPM library and full packet detection so that we only try to send packets that we know are complete. This slows down transmission time slightly, but it shouldn't be too much of a p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
2024-03-13 Fix Conflicting pin bugs and move documentation
2024-03-16 use RMT for PPM detection
    this is hardware based, so we get a much more stable input
2024-03-17 update servo code
2024-03-20 Work on servo arm
2024-03-20 add the rest of the solidworks files
    Also do some minor firmware tweaks to make sure the robot works properly
2024-03-21 some cad tweaks
2024-03-22 more changes
2024-03-23 fix pin assignments
    I did some re-soldering
2024-03-24 competition-day controller remapping
2024-03-26 add concept for next bot
    come on, I just finished building the first one! Already I have another on the table?
2024-06-07 Organize files and add camera jig
2024-06-17 add an updated STL
2024-11-06 Add robot 3 concept
2025-01-15 commit straggling changes
2025-01-15 experiment with blender
    and the sketcher addon
2025-01-20 Work on AuntFanny CAD
    got fan section finished
2025-01-22 more ideas for RB3
2025-01-29 work on sketches
2025-02-04 more work on CAD
    make wheel molds
2025-02-05 Work on robot CAD
2025-02-05 work on CAD and club BOM
2025-02-21 Firmware split + last commit before RB3 bevel
2025-03-11 lots of CAD and firmware work
    back to basics: re-establish communication between two ESP32s because that was broken in the higher-level code.
2025-03-12 discover problem with esp-now
    the new IDF I'm using apparently doesn't support encrypted targets...
2025-03-12 fix esp-radio class for all firmware types
    todo: fix base transmitter code: the PPM is broken
2025-03-19 CAD work (export for printing)
2025-03-20 add funny geometry to the robot
2025-03-22 firmware and testing
    something's broken. I don't know what...
2025-03-24 the robot works
2025-10-23 Lots of work on Robot 4
    Everything, really...
2025-10-24 CAD work
    adding screw holes, dimensions, etc.
2025-10-28 work on robot models
    todo: pete head sculpting
2025-11-11 CAD work
2025-11-11 More robot CAD work
2025-11-14 Lots of work on RB4
    so much to do in so little time
2025-11-14 more STLs and firmware testing
2025-11-17 Finish the thing before competition day
    This robot is cursed
2026-05-06 Add beauty render
